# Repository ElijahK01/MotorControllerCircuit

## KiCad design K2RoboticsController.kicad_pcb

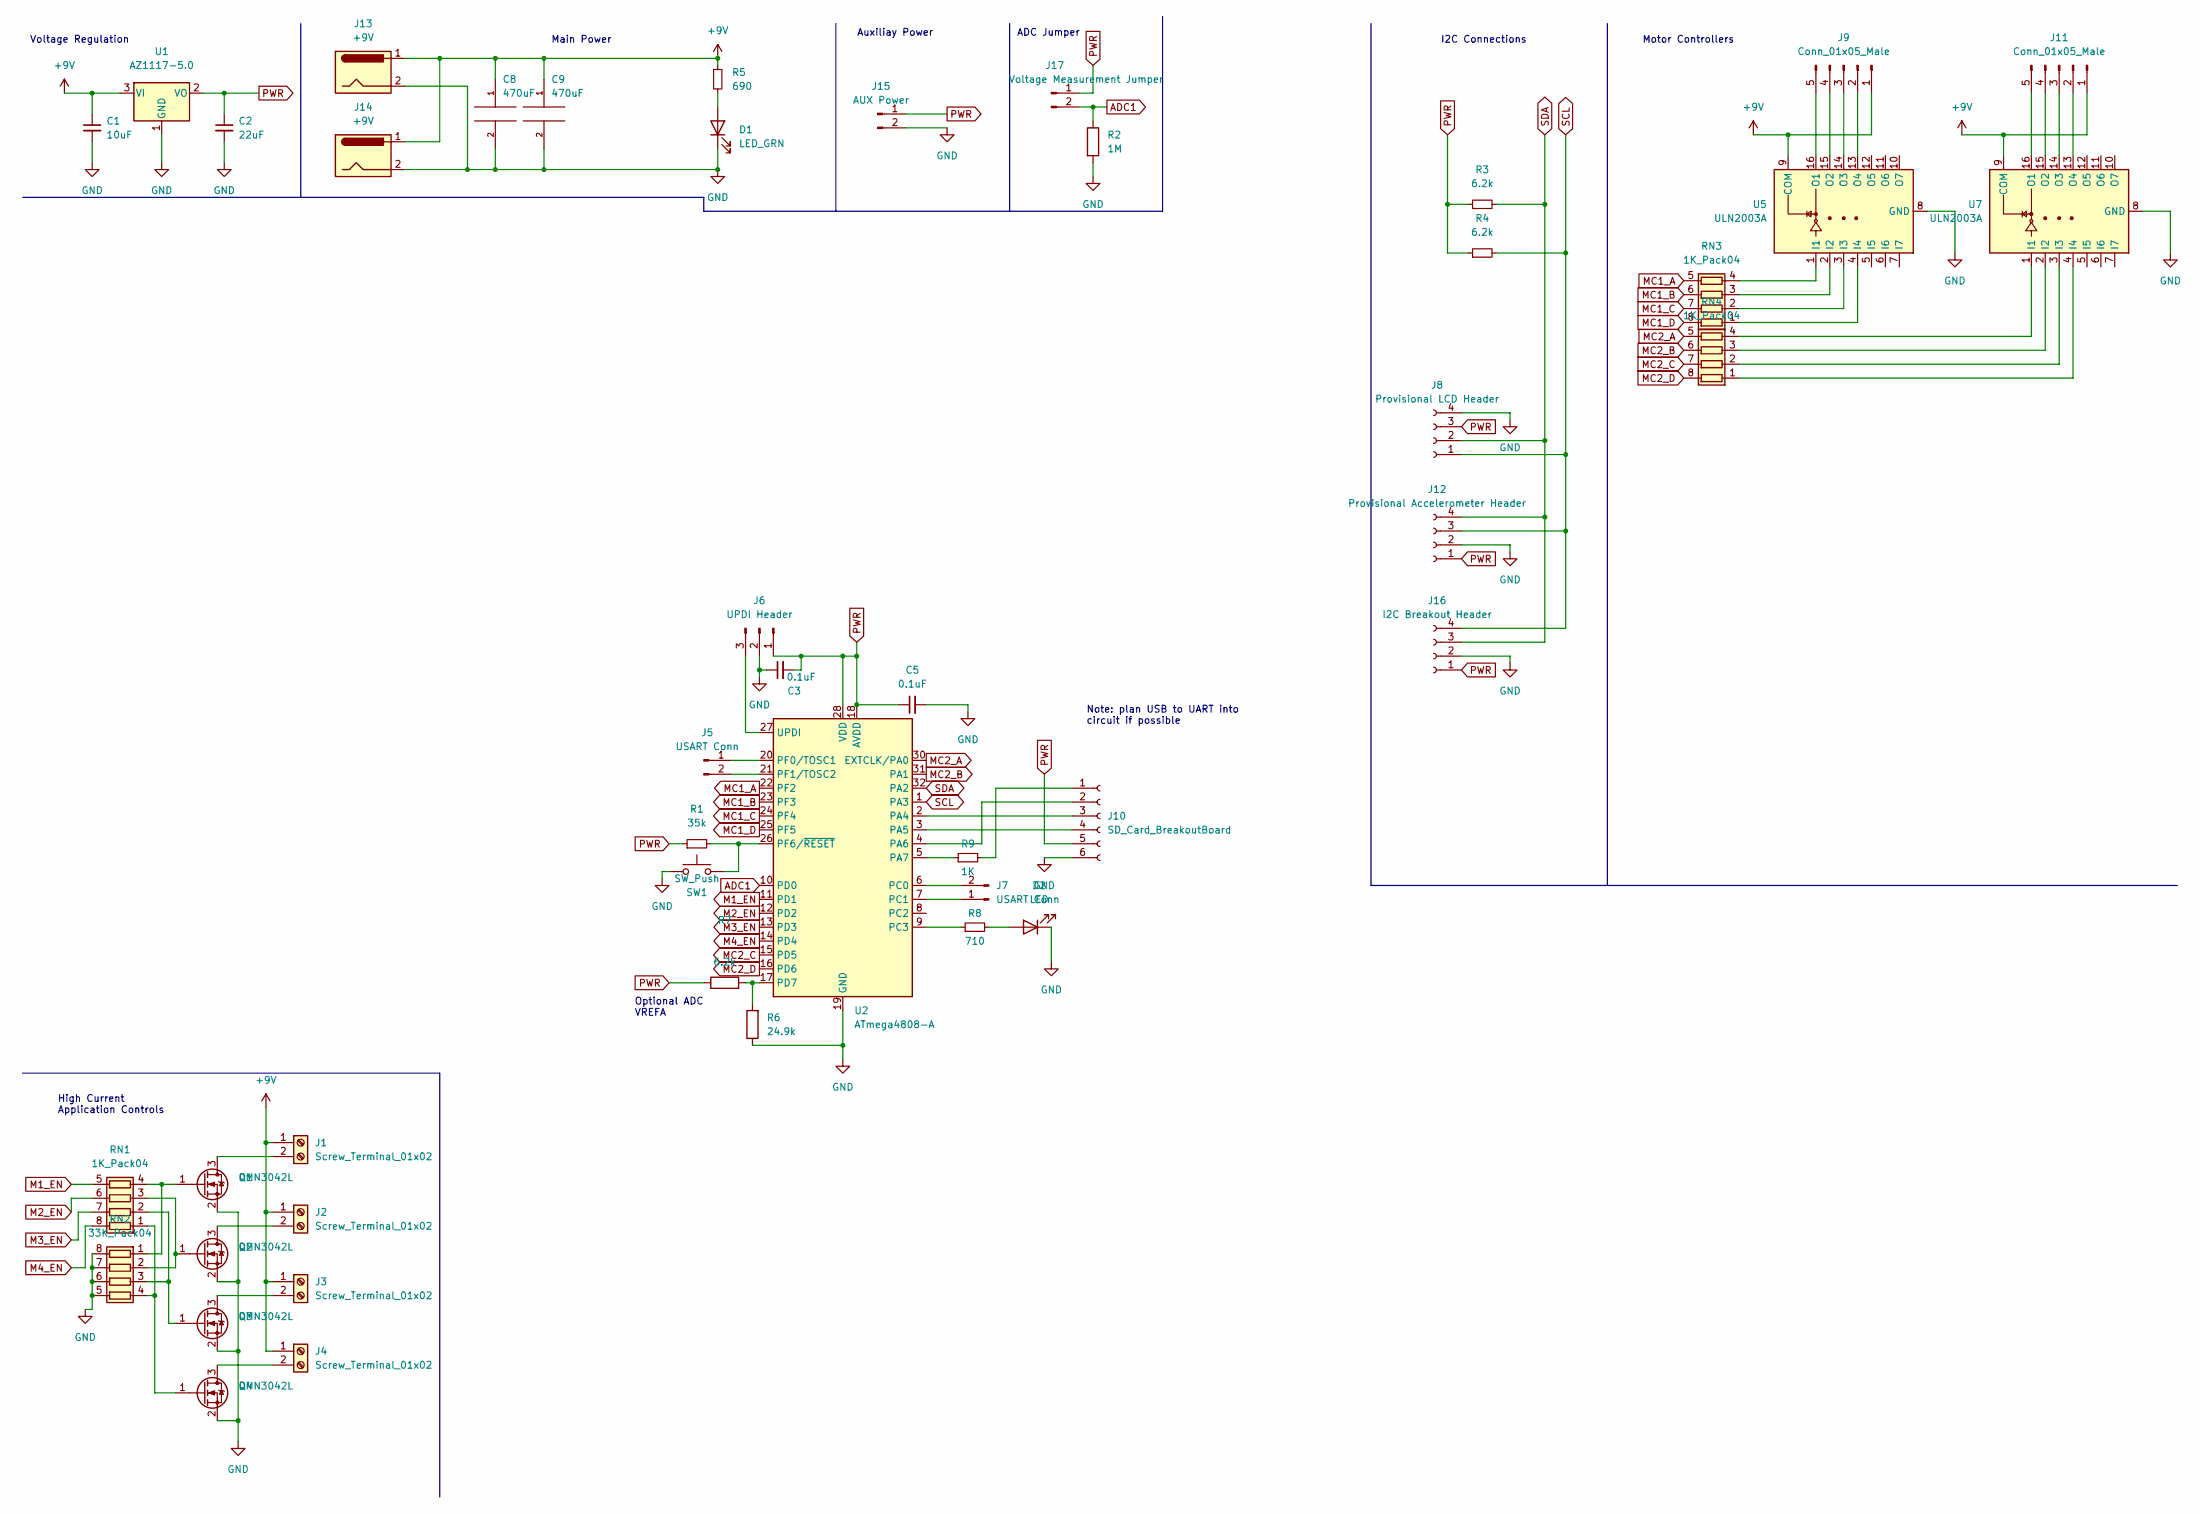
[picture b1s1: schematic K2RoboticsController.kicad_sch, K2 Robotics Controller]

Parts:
C1: 10uF; C_1206_3216Metric_Pad1.33x1.80mm_HandSolder
C2: 22uF; C_1206_3216Metric_Pad1.33x1.80mm_HandSolder
C3, C5: 0.1uF; C_1206_3216Metric_Pad1.33x1.80mm_HandSolder
C8, C9: 470uF; CP_Radial_D8.0mm_P3.50mm
D1: LED_GRN; LED_0805_2012Metric_Pad1.15x1.40mm_HandSolder
D2: LED; LED_0805_2012Metric_Pad1.15x1.40mm_HandSolder
J1, J2, J3, J4: Screw_Terminal_01x02; TerminalBlock_Altech_AK300-2_P5.00mm
J5, J7: USART Conn; PinHeader_1x02_P2.54mm_Vertical
J6: UPDI Header; PinHeader_1x03_P2.54mm_Vertical
J8: Provisional LCD Header; PinHeader_1x04_P2.54mm_Horizontal
J9, J11: Conn_01x05_Male; JST_XH_B5B-XH-A_1x05_P2.50mm_Vertical
J10: SD_Card_BreakoutBoard; PinHeader_1x06_P2.00mm_Vertical
J12: Provisional Accelerometer Header; PinHeader_1x04_P2.00mm_Vertical
J13, J14: +9V; BarrelJack_CUI_PJ-063AH_Horizontal_CircularHoles
J15: AUX Power; PinHeader_1x02_P2.54mm_Vertical
J16: I2C Breakout Header; PinHeader_1x04_P2.00mm_Vertical
J17: Voltage Measurement Jumper; PinHeader_1x02_P2.54mm_Vertical
Q1, Q2, Q3, Q4: DMN3042L; SOT-23
R1: 35k; R_1206_3216Metric_Pad1.30x1.75mm_HandSolder
R2: 1M; R_1206_3216Metric
R3, R4, R7: 6.2k; R_1206_3216Metric_Pad1.30x1.75mm_HandSolder
R5: 690; R_1206_3216Metric_Pad1.30x1.75mm_HandSolder
R6: 24.9k; R_1206_3216Metric_Pad1.30x1.75mm_HandSolder
R8: 710; R_1206_3216Metric_Pad1.30x1.75mm_HandSolder
R9: 1K; R_1206_3216Metric_Pad1.30x1.75mm_HandSolder
RN1, RN3, RN4: 1K_Pack04; R_Array_Convex_4x1206
RN2: 33K_Pack04; R_Array_Convex_4x1206
SW1: SW_Push; SW_Push_1P1T_NO_CK_KMR2
U1: AZ1117-5.0; SOT-223-3_TabPin2
U2: ATmega4808-A; TQFP-32_7x7mm_P0.8mm
U5, U7: ULN2003A; DIP-16_W7.62mm_Socket

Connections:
+9V: C1.1, C8.1, C9.1, J1.1, J2.1, J3.1, J4.1, J9.1, J11.1, J13.1, J14.1, R5.1, U1.3 (VI), U5.9 (COM), U7.9 (COM)
ADC1: J17.2, R2.1, U2.10 (PD0)
GND: C1.2, C2.2, C3.1, C5.2, C8.2, C9.2, D1.1 (K), D2.1 (K), J6.2, J8.4, J10.6, J12.2, J13.2, J14.2, J15.2, J16.2, Q1.2 (S), Q2.2 (S), Q3.2 (S), Q4.2 (S), R2.2, R6.1, RN2.5 (R4.2), RN2.6 (R3.2), RN2.7 (R2.2), RN2.8 (R1.2), SW1.1, U1.1 (GND), U2.19 (GND), U2.29 (GND), U5.8 (GND), U7.8 (GND)
M1_EN: RN1.5 (R4.2), U2.11 (PD1)
M2_EN: RN1.6 (R3.2), U2.12 (PD2)
M3_EN: RN1.7 (R2.2), U2.13 (PD3)
M4_EN: RN1.8 (R1.2), U2.14 (PD4)
MC1_A: RN3.5 (R4.2), U2.22 (PF2)
MC1_B: RN3.6 (R3.2), U2.23 (PF3)
MC1_C: RN3.7 (R2.2), U2.24 (PF4)
MC1_D: RN3.8 (R1.2), U2.25 (PF5)
MC2_A: RN4.5 (R4.2), U2.30 (EXTCLK/PA0)
MC2_B: RN4.6 (R3.2), U2.31 (PA1)
MC2_C: RN4.7 (R2.2), U2.15 (PD5)
MC2_D: RN4.8 (R1.2), U2.16 (PD6)
unnamed: D1.2 (A), R5.2
unnamed: D2.2 (A), R8.2
unnamed: J1.2, Q1.3 (D)
unnamed: J2.2, Q2.3 (D)
unnamed: J3.2, Q3.3 (D)
unnamed: J4.2, Q4.3 (D)
unnamed: J5.1, U2.20 (PF0/TOSC1)
unnamed: J5.2, U2.21 (PF1/TOSC2)
unnamed: J6.3, U2.27 (UPDI)
unnamed: J7.1, U2.7 (PC1)
unnamed: J7.2, U2.6 (PC0)
unnamed: J9.2, U5.13 (O4)
unnamed: J9.3, U5.14 (O3)
unnamed: J9.4, U5.15 (O2)
unnamed: J9.5, U5.16 (O1)
unnamed: J10.1, R9.2
unnamed: J10.2, U2.4 (PA6)
unnamed: J10.3, U2.2 (PA4)
unnamed: J10.4, U2.3 (PA5)
unnamed: J11.2, U7.13 (O4)
unnamed: J11.3, U7.14 (O3)
unnamed: J11.4, U7.15 (O2)
unnamed: J11.5, U7.16 (O1)
unnamed: Q1.1 (G), RN1.4 (R4.1), RN2.1 (R1.1)
unnamed: Q2.1 (G), RN1.3 (R3.1), RN2.2 (R2.1)
unnamed: Q3.1 (G), RN1.2 (R2.1), RN2.3 (R3.1)
unnamed: R1.2, SW1.2, U2.26 (PF6/~RESET)
unnamed: R6.2, R7.2, U2.17 (PD7)
unnamed: R8.1, U2.9 (PC3)
unnamed: R9.1, U2.5 (PA7)
unnamed: Q4.1 (G), RN1.1 (R1.1), RN2.4 (R4.1)
unnamed: RN3.1 (R1.1), U5.4 (I4)
unnamed: RN3.2 (R2.1), U5.3 (I3)
unnamed: RN3.3 (R3.1), U5.2 (I2)
unnamed: RN3.4 (R4.1), U5.1 (I1)
unnamed: RN4.1 (R1.1), U7.4 (I4)
unnamed: RN4.2 (R2.1), U7.3 (I3)
unnamed: RN4.3 (R3.1), U7.2 (I2)
unnamed: RN4.4 (R4.1), U7.1 (I1)
PWR: C2.1, C3.2, C5.1, J6.1, J8.3, J10.5, J12.1, J15.1, J16.1, J17.1, R1.1, R3.1, R4.1, R7.1, U1.2 (VO), U2.18 (AVDD), U2.28 (VDD)
SCL: J8.1, J12.3, J16.4, R4.2, U2.1 (PA3)
SDA: J8.2, J12.4, J16.3, R3.2, U2.32 (PA2)

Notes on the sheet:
Optional ADC VREFA
Note: plan USB to UART into circuit if possible
ADC Jumper
Voltage Regulation
I2C Connections
Auxiliay Power
Motor Controllers
Main Power
High Current Application Controls

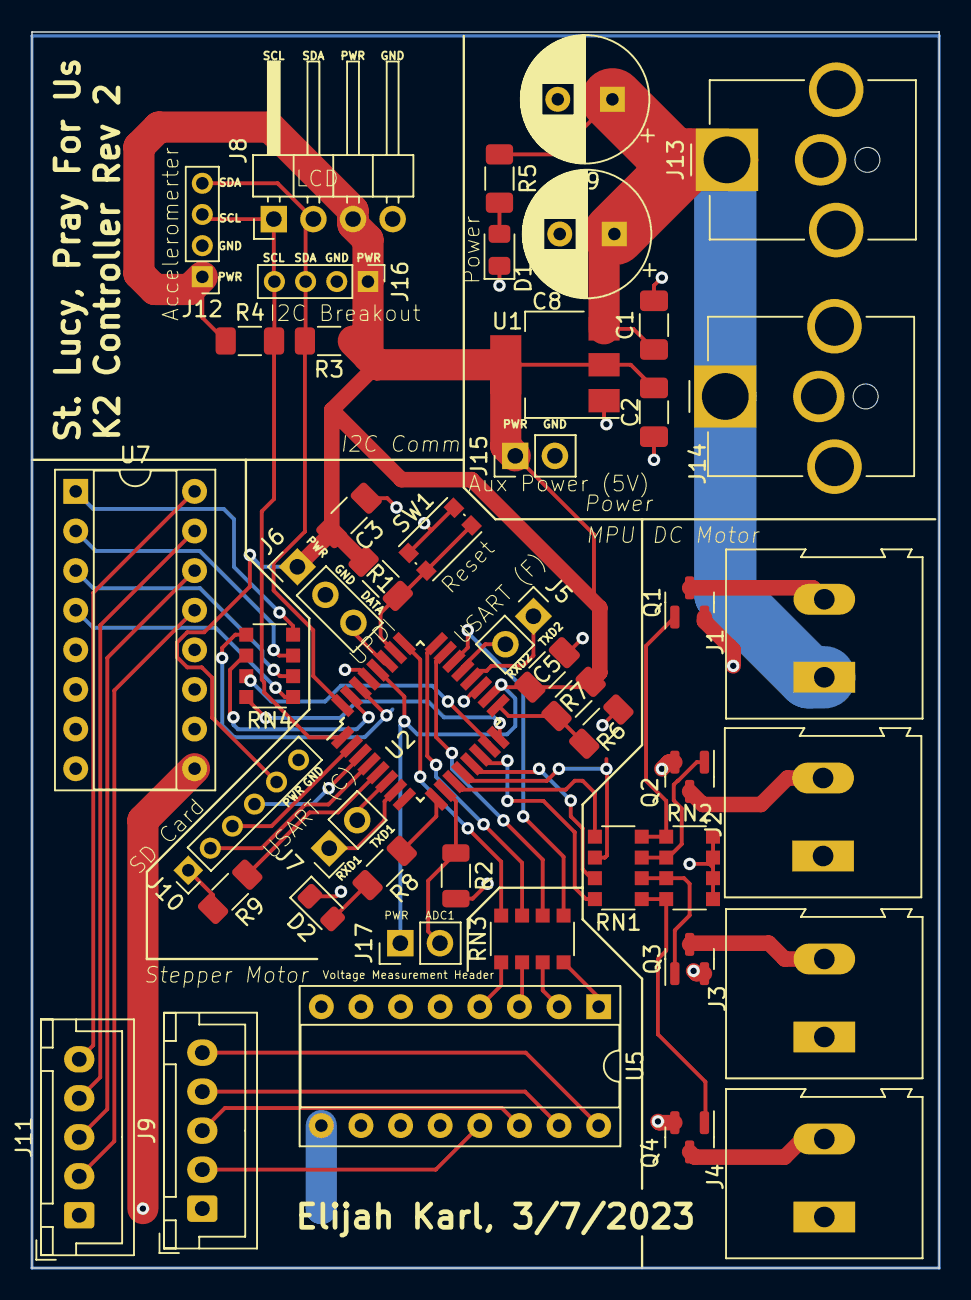
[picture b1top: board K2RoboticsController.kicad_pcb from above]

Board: 2 copper layers, 58.2 x 79.2 mm, 47 parts (0 on the bottom side), 57 nets.
